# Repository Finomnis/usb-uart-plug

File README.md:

# usb-uart-plug
A cable termination that converts a USB-C into USB+UART pads

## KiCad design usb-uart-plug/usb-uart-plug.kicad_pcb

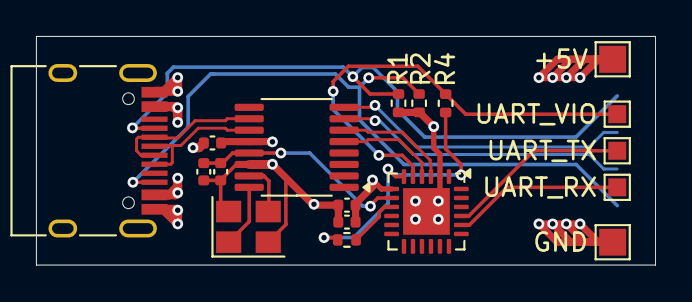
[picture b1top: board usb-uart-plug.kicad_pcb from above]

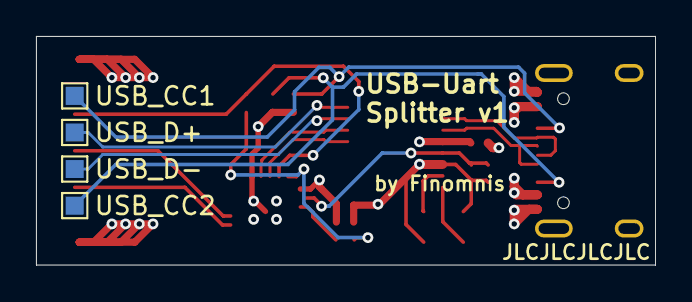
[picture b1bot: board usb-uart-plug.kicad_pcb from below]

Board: 4 copper layers, 34.4 x 12.7 mm, 22 parts (4 on the bottom side), 18 nets.

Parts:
C1, C5: 0.1u; C_0402_1005Metric
C2: 10u; C_0402_1005Metric
C3: 1u; C_0402_1005Metric
C4: 4.7u; C_0402_1005Metric
J1: USB_C_Receptacle_USB2.0_14P; USB_C_Receptacle_HRO_TYPE-C-31-M-12
J2: UART_VIO; TestPoint_Pad_1.0x1.0mm
J3: UART_RX; TestPoint_Pad_1.0x1.0mm
J4: +5V; TestPoint_Pad_1.5x1.5mm
J5: UART_TX; TestPoint_Pad_1.0x1.0mm
J6: USB_CC1; TestPoint_Pad_1.0x1.0mm
J7: USB_D+; TestPoint_Pad_1.0x1.0mm
J8: USB_D-; TestPoint_Pad_1.0x1.0mm
J9: USB_CC2; TestPoint_Pad_1.0x1.0mm
J10: GND; TestPoint_Pad_1.5x1.5mm
R1, R2: 5.1k; R_0402_1005Metric
R3: 1k; R_0402_1005Metric
R4: 0; R_0402_1005Metric
U1: CH334R; QSOP-16_3.9x4.9mm_P0.635mm
U2: CP2102N-Axx-xQFN24; QFN-24-1EP_4x4mm_P0.5mm_EP2.6x2.6mm
Y1: 12MHz; Crystal_SMD_3225-4Pin_3.2x2.5mm

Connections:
+5V: C3.1, C4.1, C5.1, J1.A4 (VBUS), J1.A9 (VBUS), J1.B4 (VBUS), J1.B9 (VBUS), J4.1, U1.12 (V5), U2.7 (VREGIN)
/USB_CONN_D+: J1.A6 (D+), J1.B6 (D+), U1.11 (DPU+)
/USB_CONN_D-: J1.A7 (D-), J1.B7 (D-), U1.10 (DMU-)
/USB_UART_D+: U1.6 (DP2+), U2.3 (D+)
/USB_UART_D-: U1.5 (DM2-), U2.4 (D-)
CC1: J1.A5 (CC1), J6.1, R1.1
CC2: J1.B5 (CC2), J9.1, R2.1
GND: C1.2, C2.2, C3.2, C4.2, C5.2, J1.A1 (GND), J1.A12 (GND), J1.B1 (GND), J1.B12 (GND), J10.1, R1.2, R2.2, U1.14 (GND), U2.2 (GND), U2.25 (GND), Y1.2, Y1.4
unnamed: C1.1, C2.1, U1.13 (VDD33), U2.8 (VBUS)
unnamed: U1.16 (XI), Y1.1
unnamed: U1.15 (XO), Y1.3
unnamed: R3.1, R4.1, U2.6 (VDD)
unnamed: R3.2, U2.9 (~RST)
UART_RX: J3.1, U2.20 (RXD)
UART_TX: J5.1, U2.21 (TXD)
UART_VIO: J2.1, R4.2, U2.5 (VIO)
USB_D+: J7.1, U1.8 (DP1+)
USB_D-: J8.1, U1.7 (DM1-)

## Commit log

2024-07-23 Minor text fix; release v1
2024-07-23 Adjust silkscreen text
2024-07-23 Add silkscreen text
2024-07-23 Design plug
